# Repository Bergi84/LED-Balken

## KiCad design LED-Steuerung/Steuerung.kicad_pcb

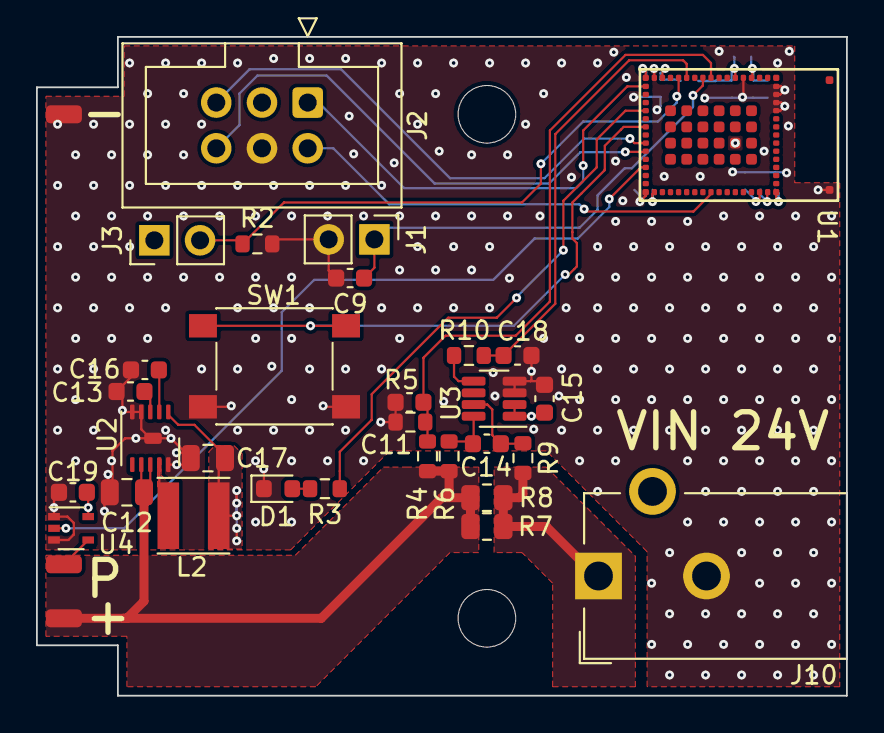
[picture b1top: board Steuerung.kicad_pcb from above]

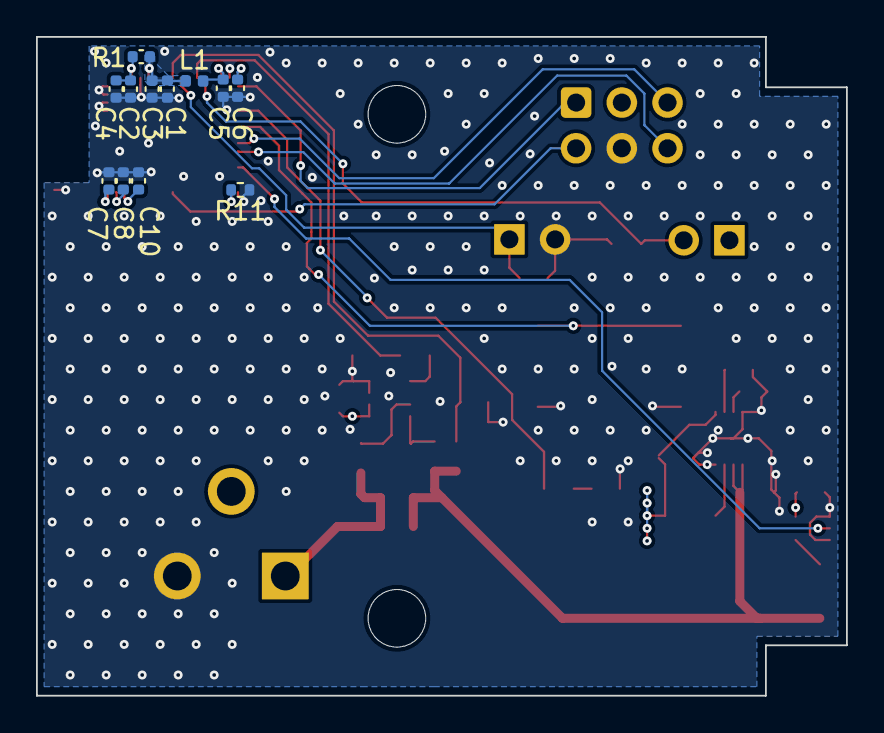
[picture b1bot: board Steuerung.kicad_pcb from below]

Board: 4 copper layers, 45.0 x 36.6 mm, 47 parts (12 on the bottom side), 29 nets.

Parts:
C1, C2, C5: 100n; C_0402_1005Metric
C3, C4, C6: 1µ; C_0402_1005Metric
C7, C8, C10: 3p3; C_0402_1005Metric
C9, C11, C15, C16, C18, C19: 100n; C_0603_1608Metric
C12: 1µ; C_0805_2012Metric
C13: 470n; C_0603_1608Metric
C14: DNP; C_0603_1608Metric
C17: 2µ2; C_0805_2012Metric
D1: LED; LED_0603_1608Metric
H1, H2: MountingHole; MountingHole_3.2mm_M3
J1, J3: DNP; PinHeader_1x02_P2.54mm_Vertical
J2: Conn_02x03_Odd_Even; IDC-Header_2x03_P2.54mm_Vertical
J4, J7, J8: Conn_01x01_Female; Solderpad_1x2
J10: Barrel_Jack_Switch; BarrelJack_CUI_PJ-102AH_Horizontal
L1: 600R; L_0402_1005Metric
L2: 47µ; L_Taiyo-Yuden_NR-40xx
R1: DNP; C_0402_1005Metric
R2: 10k; R_0603_1608Metric
R3: 240R; R_0603_1608Metric
R4: 24k; R_0603_1608Metric
R5: 1k6; R_0603_1608Metric
R6, R9: 0R; R_0603_1608Metric
R7: 0R01; R_0805_2012Metric
R8: DNP; R_0805_2012Metric
R10: 1k5; R_0603_1608Metric
R11: 10k; R_0402_1005Metric
SW1: SW_Push; SW_Push_1P1T_NO_6x6mm_H9.5mm
U1: STM32WB5MMG; ST_LGA86
U2: L7983; DFN-10-1EP_3x3mm_P0.5mm_EP0.62x0.98mm
U3: INA186A3IDDF; SOT-23-8
U4: 74AHCT1G125; SOT-353_SC-70-5

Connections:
+3.3V: C5.1, C6.1, C15.1, C17.1, C19.1, J2.3, J3.1, L1.2, L2.2, U1.15 (VBAT), U1.17 (VDD), U2.1 (VOUT/FB), U3.1 (VS), U3.2 (EN), U4.5 (VCC)
+3.3VA: C1.1, C3.1, L1.1, R1.1, U1.6 (VDDA)
+24V: C12.1, J4.1, R4.2, R6.2, R7.1, R8.1, U2.7 (EN/UVLO), U2.8 (VIN)
/BTN0: SW1.2, U1.23 (PC11)
/Boot0: J3.2, R2.1, U1.13 (PH3-BOOT0)
/I_sens: C18.1, R10.1, U1.12 (PC0)
/LED0: R3.1, U1.21 (PB3)
/NRST: C9.1, J1.1, U1.10 (NRST)
/PWM: J7.1, U4.4
/RX: J2.1, U1.18 (PB7)
/SWCLK: J2.6, U1.26 (PA14)
/SWDIO: J2.5, U1.25 (PA13)
/TX: J2.2, U1.39 (PB6)
/V_sens: C11.1, R4.1, R5.2, U1.9 (PC1)
GND: C1.2, C2.2, C3.2, C4.2, C5.2, C6.2, C7.2, C8.2, C9.2, C10.2, C11.2, C12.2, C13.2, C15.2, C16.2, C17.2, C18.2, C19.2, D1.1 (K), J1.2, J2.4, J8.1, J10.2, R2.2, R5.1, R11.1, SW1.1, U1.5 (VSS), U1.16 (VSS), U1.31 (VSS), U1.57 (VSS), U1.58 (ANT_IN), U1.59 (RF_OUT), U1.60 (VSS), U1.84 (VSS), U1.86 (VSS), U2.4 (FSW), U2.5 (LNM/NLCM), U2.10 (GND), U2.11 (EP), U3.3 (REF), U3.4 (GND), U4.1, U4.3 (GND)
unnamed: C2.1, C4.1, R1.2, U1.4 (VREF+)
unnamed: C7.1, U1.47 (PB10)
unnamed: C8.1, U1.46 (PB11)
unnamed: C10.1, U1.45 (PC5)
unnamed: C13.1, U2.3 (VCC)
unnamed: C14.1, R6.1, U3.8 (-IN)
unnamed: C14.2, R9.1, U3.7 (+IN)
unnamed: C16.1, U2.2 (VBIAS)
unnamed: D1.2 (A), R3.2
unnamed: L2.1, U2.9 (LX)
unnamed: R10.2, U3.5 (OUT)
unnamed: R11.2, U1.32 (VDDUSB)
unnamed: U1.28 (PA10), U4.2
VDC: J10.1, R7.2, R8.2, R9.2

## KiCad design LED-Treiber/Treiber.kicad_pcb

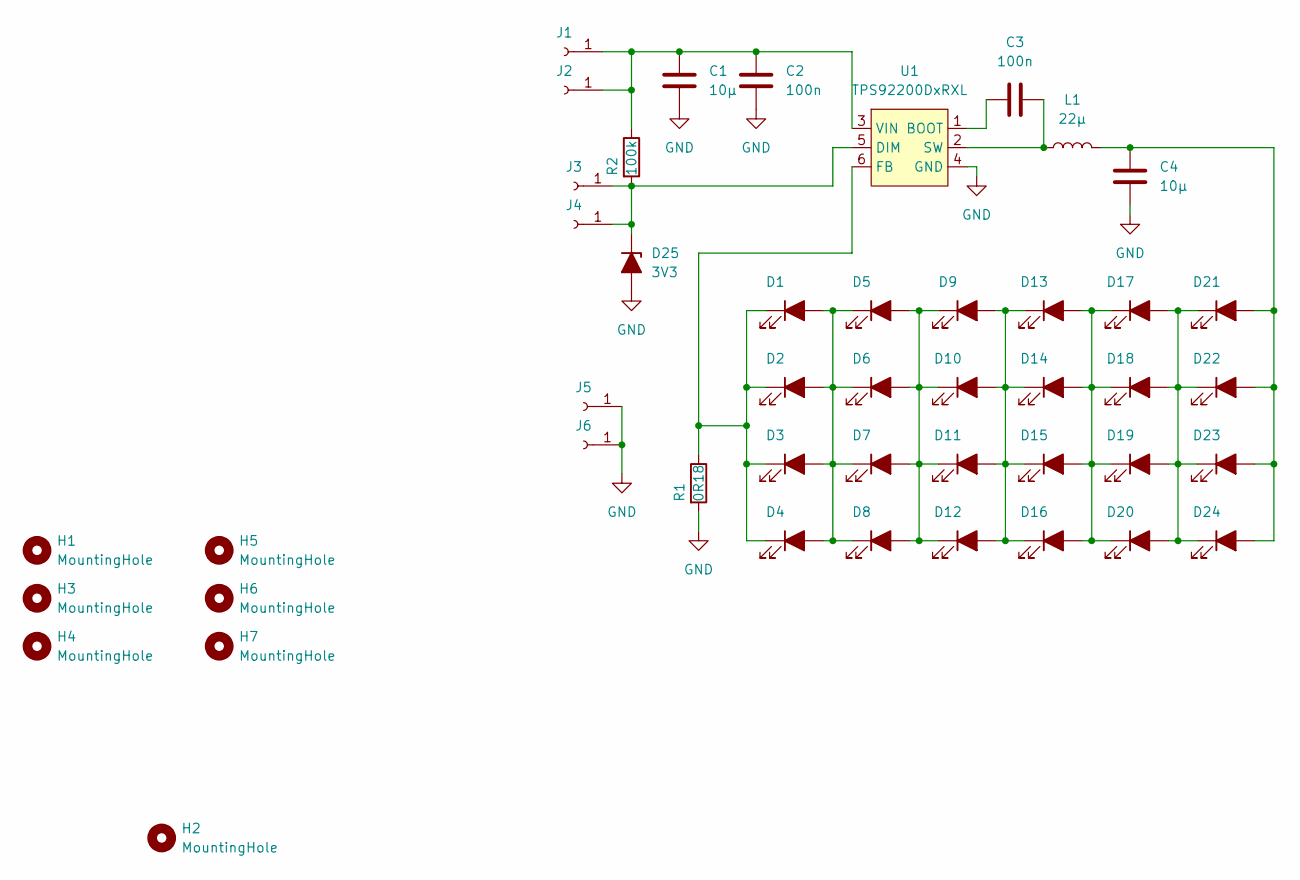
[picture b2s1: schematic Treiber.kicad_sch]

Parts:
C1, C4: 10µ; C_1210_3225Metric; Voltage 50V
C2, C3: 100n; C_0603_1608Metric
D1, D2, D3, D4, D5, D6, D7, D8, D9, D10, D11, D12, D13, D14, D15, D16, D17, D18, D19, D20, D21, D22, D23, D24: JE2835AWT-R-U40GA0000-N0000001; LED_PLCC_2835
D25: 3V3; D_SOD-323
H1, H3, H4, H5, H6, H7: MountingHole; MountingHole_3.2mm_M3
H2: MountingHole; MountingHole_4.3mm_M4
J1, J2, J3, J4, J5, J6: Conn_01x01_Female; Solderpad_1x2
L1: 22µ; L_Taiyo-Yuden_NR-60xx
R1: 0R18; R_0603_1608Metric
R2: 100k; R_0603_1608Metric
U1: TPS92200DxRXL; VQFN-HR

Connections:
GND: C1.1, C2.1, C4.1, D25.2 (A), J5.1, J6.1, R1.2, U1.4 (GND)
unnamed: C1.2, C2.2, J1.1, J2.1, R2.1, U1.3 (VIN)
unnamed: C3.1, U1.1 (BOOT)
unnamed: C3.2, L1.1, U1.2 (SW)
unnamed: C4.2, D21.2 (A), D22.2 (A), D23.2 (A), D24.2 (A), L1.2
unnamed: D1.1 (K), D2.1 (K), D3.1 (K), D4.1 (K), R1.1, U1.6 (FB)
unnamed: D1.2 (A), D2.2 (A), D3.2 (A), D4.2 (A), D5.1 (K), D6.1 (K), D7.1 (K), D8.1 (K)
unnamed: D5.2 (A), D6.2 (A), D7.2 (A), D8.2 (A), D9.1 (K), D10.1 (K), D11.1 (K), D12.1 (K)
unnamed: D9.2 (A), D10.2 (A), D11.2 (A), D12.2 (A), D13.1 (K), D14.1 (K), D15.1 (K), D16.1 (K)
unnamed: D13.2 (A), D14.2 (A), D15.2 (A), D16.2 (A), D17.1 (K), D18.1 (K), D19.1 (K), D20.1 (K)
unnamed: D17.2 (A), D18.2 (A), D19.2 (A), D20.2 (A), D21.1 (K), D22.1 (K), D23.1 (K), D24.1 (K)
unnamed: D25.1 (K), J3.1, J4.1, R2.2, U1.5 (DIM)

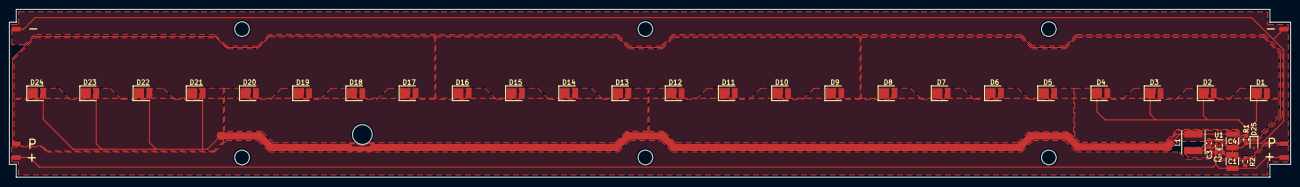
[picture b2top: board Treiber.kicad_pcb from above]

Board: 2 copper layers, 279.5 x 36.6 mm, 46 parts (0 on the bottom side), 12 nets.

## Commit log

2022-07-30 init
2022-07-30 move
2022-07-31 LED-Treiber PCB rooted
2022-07-31 Swapped some LED's
2022-08-15 routed zigbee control
2022-08-15 removed unneeded via
